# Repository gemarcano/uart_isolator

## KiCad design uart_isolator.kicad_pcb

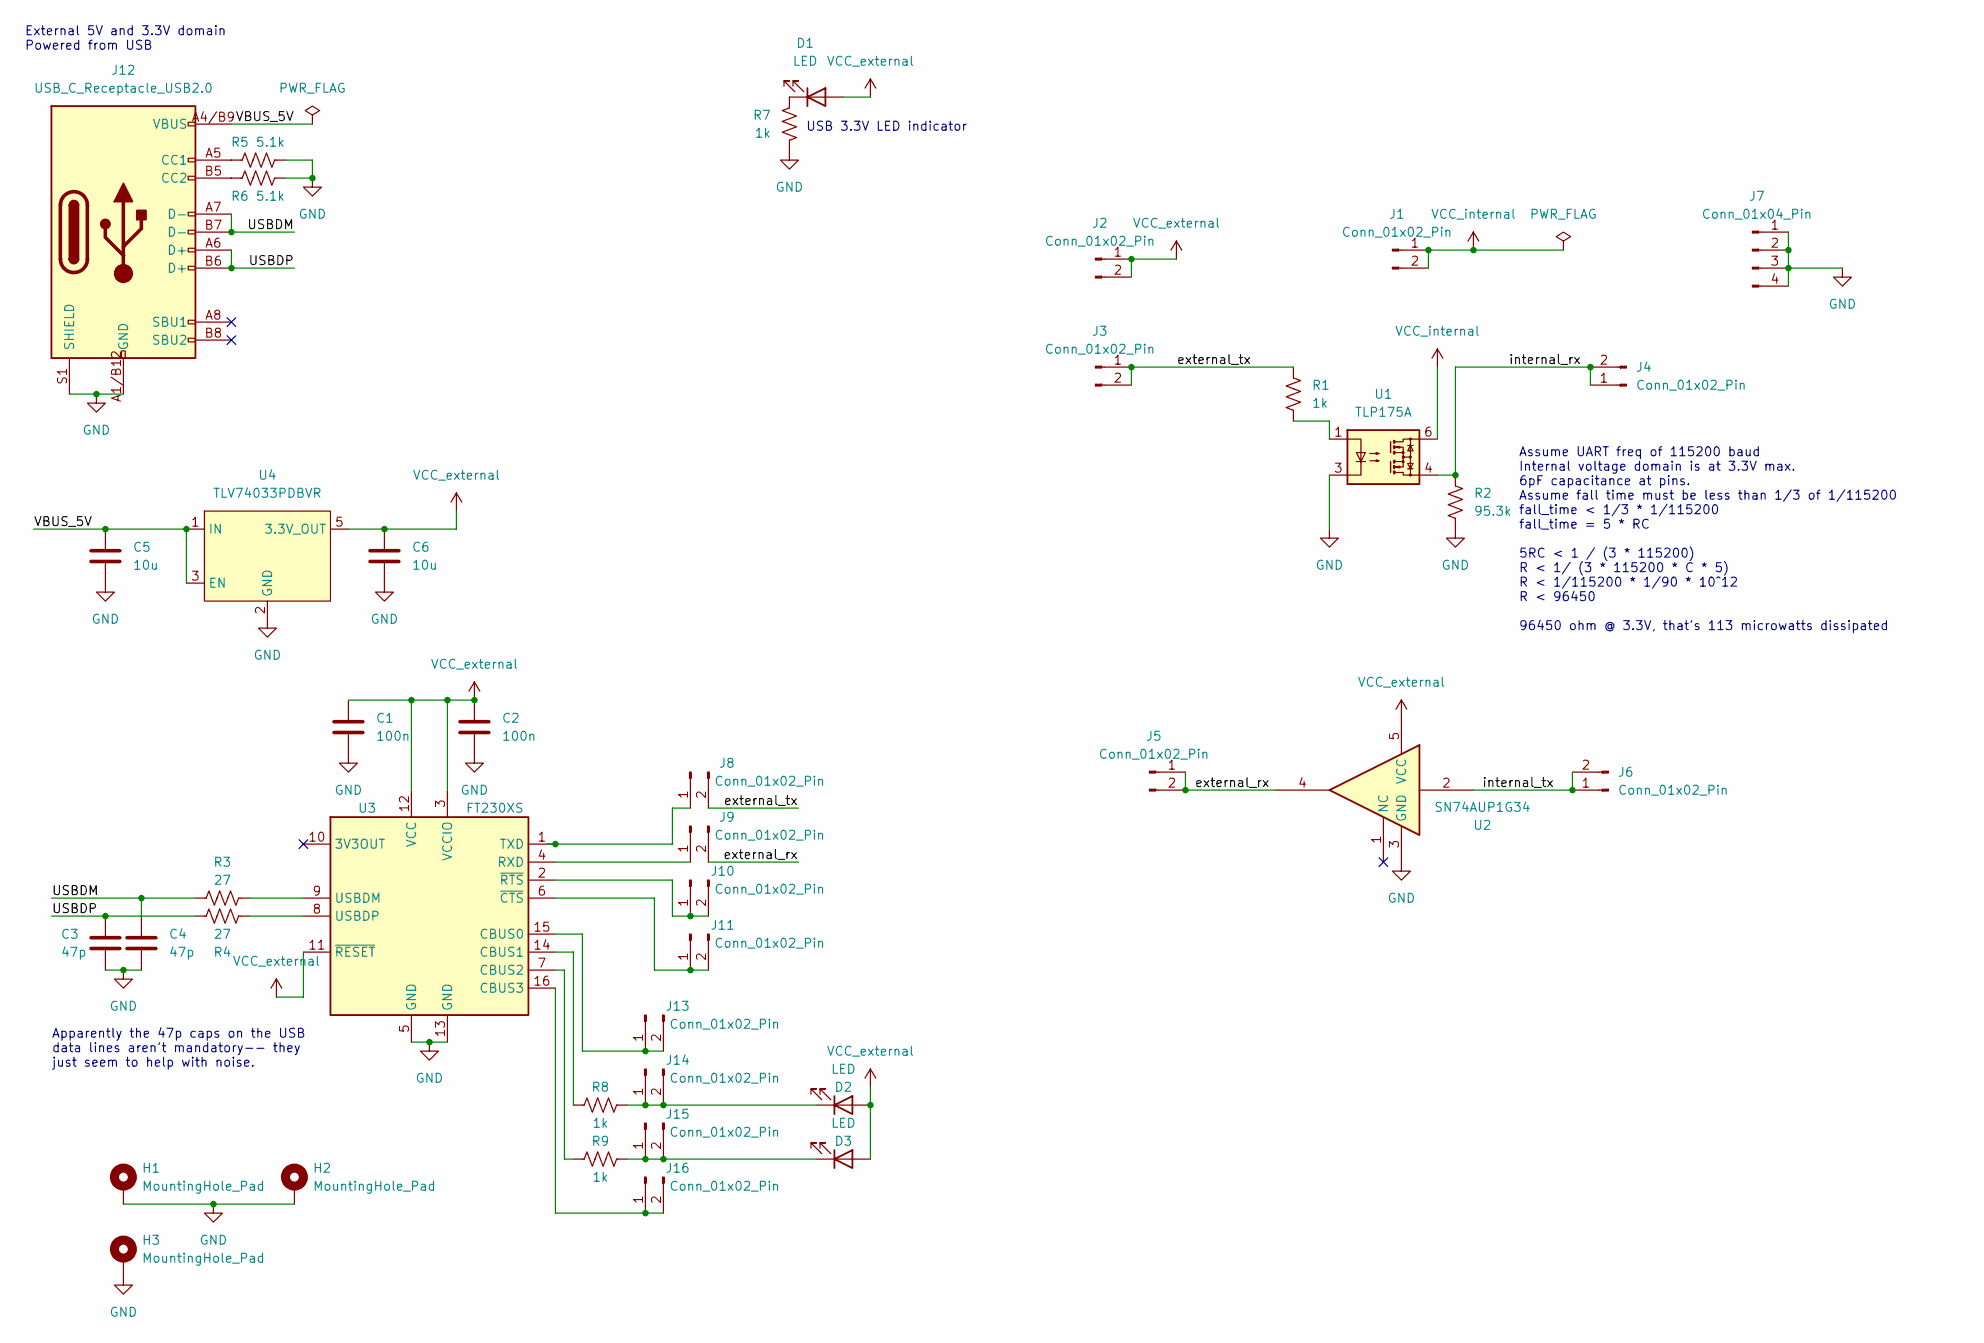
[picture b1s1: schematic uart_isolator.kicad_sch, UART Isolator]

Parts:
C1, C2: 100n; C_0603_1608Metric_Pad1.08x0.95mm_HandSolder; Digikey Product Number 1276-1935-2-ND
C3, C4: 47p; C_0603_1608Metric_Pad1.08x0.95mm_HandSolder; Digikey Product Number 1276-1037-2-ND
C5, C6: 10u; C_0603_1608Metric_Pad1.08x0.95mm_HandSolder; Digikey Product Number 1276-1119-1-ND
D1, D2, D3: LED; LED_0603_1608Metric_Pad1.05x0.95mm_HandSolder; Digikey Product Number 732-12016-2-ND
H1, H2, H3: MountingHole_Pad; MountingHole_2.2mm_M2_Pad_Via
J1, J2, J3, J4, J5, J6, J8, J9, J10, J11, J13, J14, J15, J16: Conn_01x02_Pin; PinHeader_1x02_P2.54mm_Vertical
J7: Conn_01x04_Pin; PinHeader_1x04_P2.54mm_Vertical
J12: USB_C_Receptacle_USB2.0; USB4105-GF-A; Digikey Product Number 2073-USB4105-GF-ACT-ND
R1, R7, R8, R9: 1k; R_0603_1608Metric_Pad0.98x0.95mm_HandSolder; Digikey Product Number RMCF0603FT1K00TR-ND
R2: 95.3k; R_0603_1608Metric_Pad0.98x0.95mm_HandSolder; Digikey Product Number 13-AC0603FR-0795K3LCT-ND
R3, R4: 27; R_0603_1608Metric_Pad0.98x0.95mm_HandSolder; Digikey Product Number CR0603-FX-27R0ELFTR-ND
R5, R6: 5.1k; R_0603_1608Metric_Pad0.98x0.95mm_HandSolder; Digikey Product Number RMCF0603FT5K10TR-ND
U1: TLP175A; MFSOP6-4_4.4x3.6mm_P1.27mm; Digikey Product Number TLP175A(TPLECT-ND
U2: SN74AUP1G34; SOT-23-5_HandSoldering; Digikey Product Number 296-19080-1-ND
U3: FT230XS; SSOP-16_3.9x4.9mm_P0.635mm; Digikey Product Number 768-1135-2-ND
U4: TLV74033PDBVR; SOT-23-5_HandSoldering; Digikey Product Number 296-TLV74033PDBVRCT-ND

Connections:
/USBDM: C4.1, J12.A7 (D-), J12.B7 (D-), R3.1
/USBDP: C3.1, J12.A6 (D+), J12.B6 (D+), R4.1
/VBUS_5V: C5.1, J12.A4/B9 (VBUS), J12.A9/B4 (VBUS), U4.1 (IN), U4.3 (EN)
/external_rx: J5.1, J5.2, J9.2, U2.4
/external_tx: J3.1, J3.2, J8.2, R1.1
/internal_rx: J4.1, J4.2, R2.1, U1.4
/internal_tx: J6.1, J6.2, U2.2
GND: C1.2, C2.2, C3.2, C4.2, C5.2, C6.2, H1.1, H2.1, H3.1, J7.1, J7.2, J7.3, J7.4, J12.A1/B12 (GND), J12.A12/B1 (GND), J12.S1 (SHIELD), R2.2, R5.2, R6.2, R7.2, U1.3, U2.3 (GND), U3.5 (GND), U3.13 (GND), U4.2 (GND)
unnamed: D1.1 (K), R7.1
unnamed: D2.1 (K), J14.1, J14.2, R8.1
unnamed: D3.1 (K), J15.1, J15.2, R9.1
unnamed: J8.1, U3.1 (TXD)
unnamed: J9.1, U3.4 (RXD)
unnamed: J10.1, J10.2, U3.2 (~RTS)
unnamed: J11.1, J11.2, U3.6 (~CTS)
unnamed: J12.A5 (CC1), R5.1
unnamed: J12.B5 (CC2), R6.1
unnamed: J13.1, J13.2, U3.15 (CBUS0)
unnamed: J16.1, J16.2, U3.16 (CBUS3)
unnamed: R1.2, U1.1
unnamed: R8.2, U3.14 (CBUS1)
unnamed: R9.2, U3.7 (CBUS2)
unnamed: R3.2, U3.9 (USBDM)
unnamed: R4.2, U3.8 (USBDP)
VCC_external: C1.1, C2.1, C6.1, D1.2 (A), D2.2 (A), D3.2 (A), J2.1, J2.2, U2.5 (VCC), U3.3 (VCCIO), U3.11 (~RESET), U3.12 (VCC), U4.5 (3.3V_OUT)
VCC_internal: J1.1, J1.2, U1.6

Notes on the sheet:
External 5V and 3.3V domain Powered from USB
USB 3.3V LED indicator
Assume UART freq of 115200 baud Internal voltage domain is at 3.3V max. 6pF capacitance at pins. Assume fall time must be less than 1/3 of 1/115200 fall_time < 1/3 * 1/115200 fall_time = 5 * RC 5RC < 1 / (3 * 115200) R < 1/ (3 * 115200 * C * 5) R < 1/115200 * 1/90 * 10^12 R < 96450 96450 ohm @ 3.3V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
Apparently the 47p caps on the USB data lines aren't mandatory-- they just seem to help with noise.

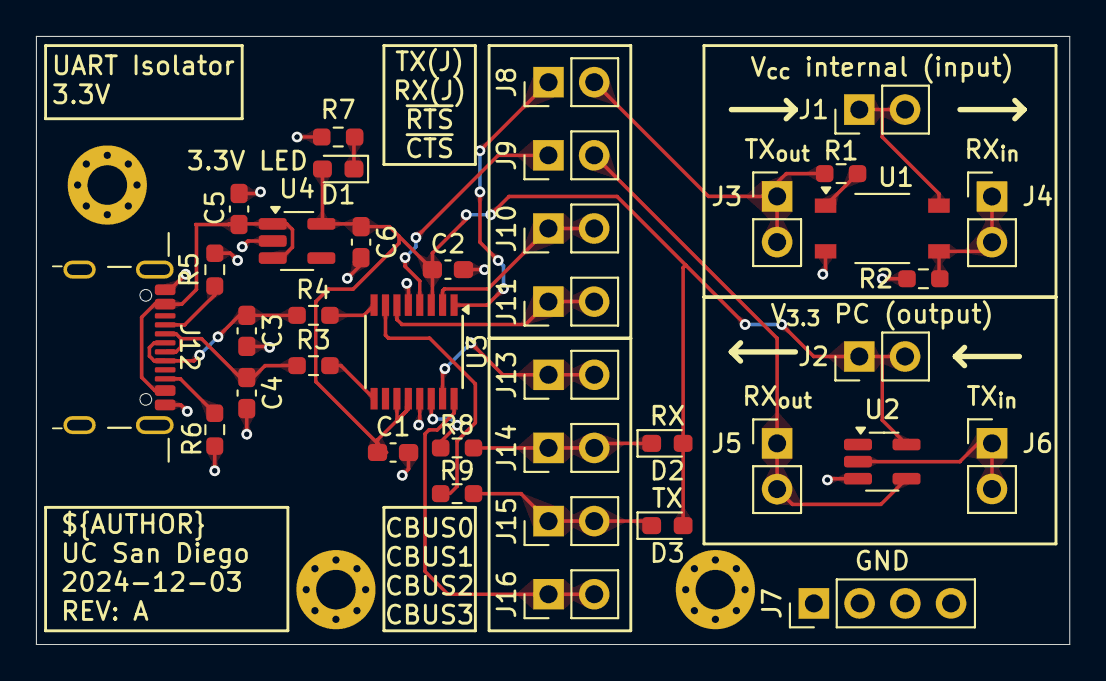
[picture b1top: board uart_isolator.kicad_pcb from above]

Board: 2 copper layers, 57.4 x 33.8 mm, 41 parts (0 on the bottom side), 26 nets.

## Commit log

2024-11-06 Change to using voltage buffer
    - Silkmask updates to clarify labels
    - Using voltage buffer to isolate TX_in from RX_out
2024-12-05 Rev A
